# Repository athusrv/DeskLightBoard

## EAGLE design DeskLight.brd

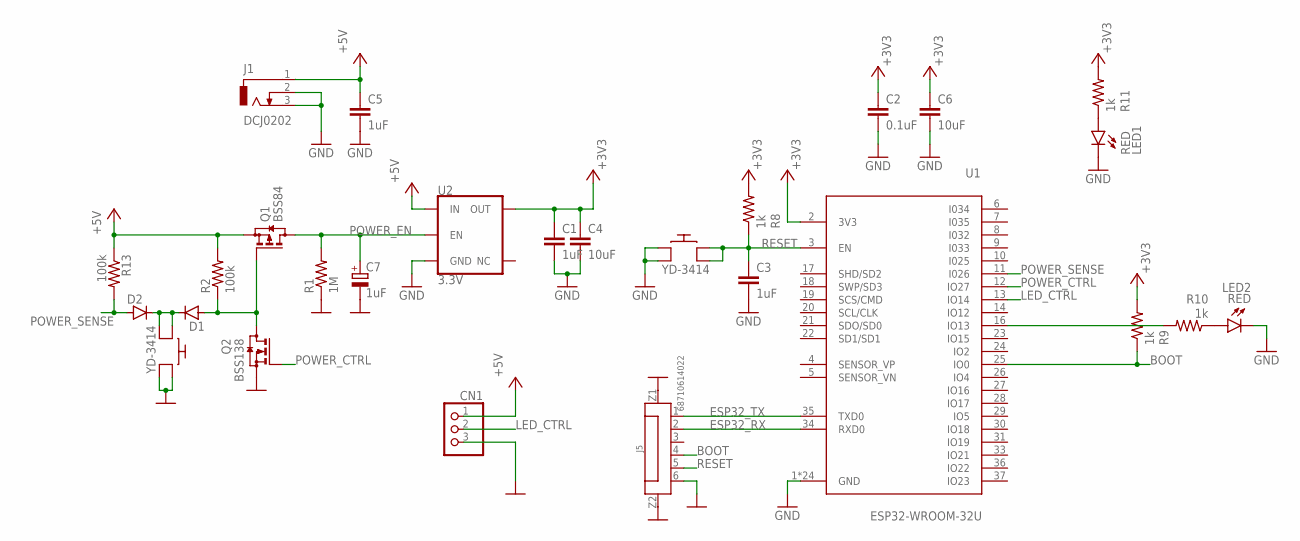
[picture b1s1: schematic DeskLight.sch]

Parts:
C1, C3, C5: 1uF; C0603
C2: 0.1uF; C0603
C4, C6: 10uF; C0805
C7: 1uF; CT3216
CN1: JST_3PIN; JSTPH3
D1, D2: D-SOD123; SOD123
J1: DCJ0202
J5: 68710614022
LED1, LED2: RED; MICRO-SIDELED
Q1: BSS84; SOT23
Q2: BSS138; SOT23
R1: 1M; R0603
R2, R13: 100k; R0603
R8, R9, R10, R11: 1k; R0603
U1: ESP32-WROOM-32U; XCVR_ESP32-WROOM-32U
U2: 3.3V; SOT23-5
U$1, U$67: YD-3414

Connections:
+3V3: C1.1, C2.1, C4.1, C6.1, R8.2, R9.2, R11.2, U1.2 (3V3), U2.5 (OUT)
+5V: C5.1, CN1.1, J1.1, Q1.2 (S), R2.2, R13.1, U2.1 (IN)
BOOT: J5.4, R9.1, U1.25 (IO0)
ESP32_RX: J5.2, U1.34 (RXD0)
ESP32_TX: J5.1, U1.35 (TXD0)
GND: C1.2, C2.2, C3.2, C4.2, C5.2, C6.2, C7.-, CN1.3, J1.2, J1.3, J5.6, J5.Z1, J5.Z2, LED1.C, LED2.C, Q2.2 (S), R1.1, U1.1 (GND), U1.15 (GND), U1.38 (GND), U1.G.1 (GND), U1.G.2 (GND), U1.G.4 (GND), U1.G.5 (GND), U1.G.6 (GND), U1.G.7 (GND), U1.G.8 (GND), U1.G.9 (GND), U1.G.10 (GND), U1.G.11 (GND), U1.G.12 (GND), U1.G.13 (GND), U1.G.14 (GND), U1.G.15 (GND), U1.G.16 (GND), U1.G.17 (GND), U1.G.18 (GND), U1.G.19 (GND), U1.G.20 (GND), U1.G.21 (GND), U1.G.22 (GND), U2.2 (GND), U$1.P$3, U$1.P$4, U$67.P$3, U$67.P$4
LED_CTRL: CN1.2, U1.13 (IO14)
unnamed: D1.2 (A), Q1.1 (G), Q2.3 (D), R2.1
unnamed: R10.2, U1.16 (IO13)
unnamed: LED1.A, R11.1
unnamed: D1.1 (C), D2.1 (C), U$67.P$1, U$67.P$2
unnamed: LED2.A, R10.1
POWER_CTRL: Q2.1 (G), U1.12 (IO27)
POWER_EN: C7.+, Q1.3 (D), R1.2, U2.3 (EN)
POWER_SENSE: D2.2 (A), R13.2, U1.11 (I026)
RESET: C3.1, J5.5, R8.1, U1.3 (EN), U$1.P$1, U$1.P$2

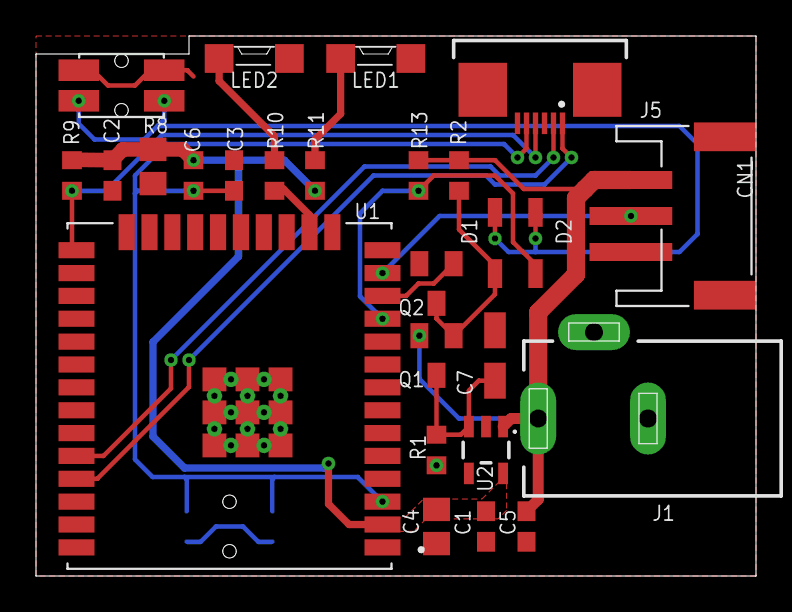
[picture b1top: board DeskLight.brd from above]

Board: 2 copper layers, 40.0 x 30.0 mm, 27 parts (1 on the bottom side), 16 nets.

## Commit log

2020-05-27 deleted unnecessary files and added gitignore files
2020-06-01 added comp. values
2021-03-16 new version with small size and for addressable led strips
2021-03-20 reviewed

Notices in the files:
parts and their libraries:
WR-FPC: Copyright: Würth Elektronik
SparkFun-IC-Power: Licensing: Creative Commons ShareAlike 4.0 International - https://creativecommons.org/licenses/by-sa/4.0
